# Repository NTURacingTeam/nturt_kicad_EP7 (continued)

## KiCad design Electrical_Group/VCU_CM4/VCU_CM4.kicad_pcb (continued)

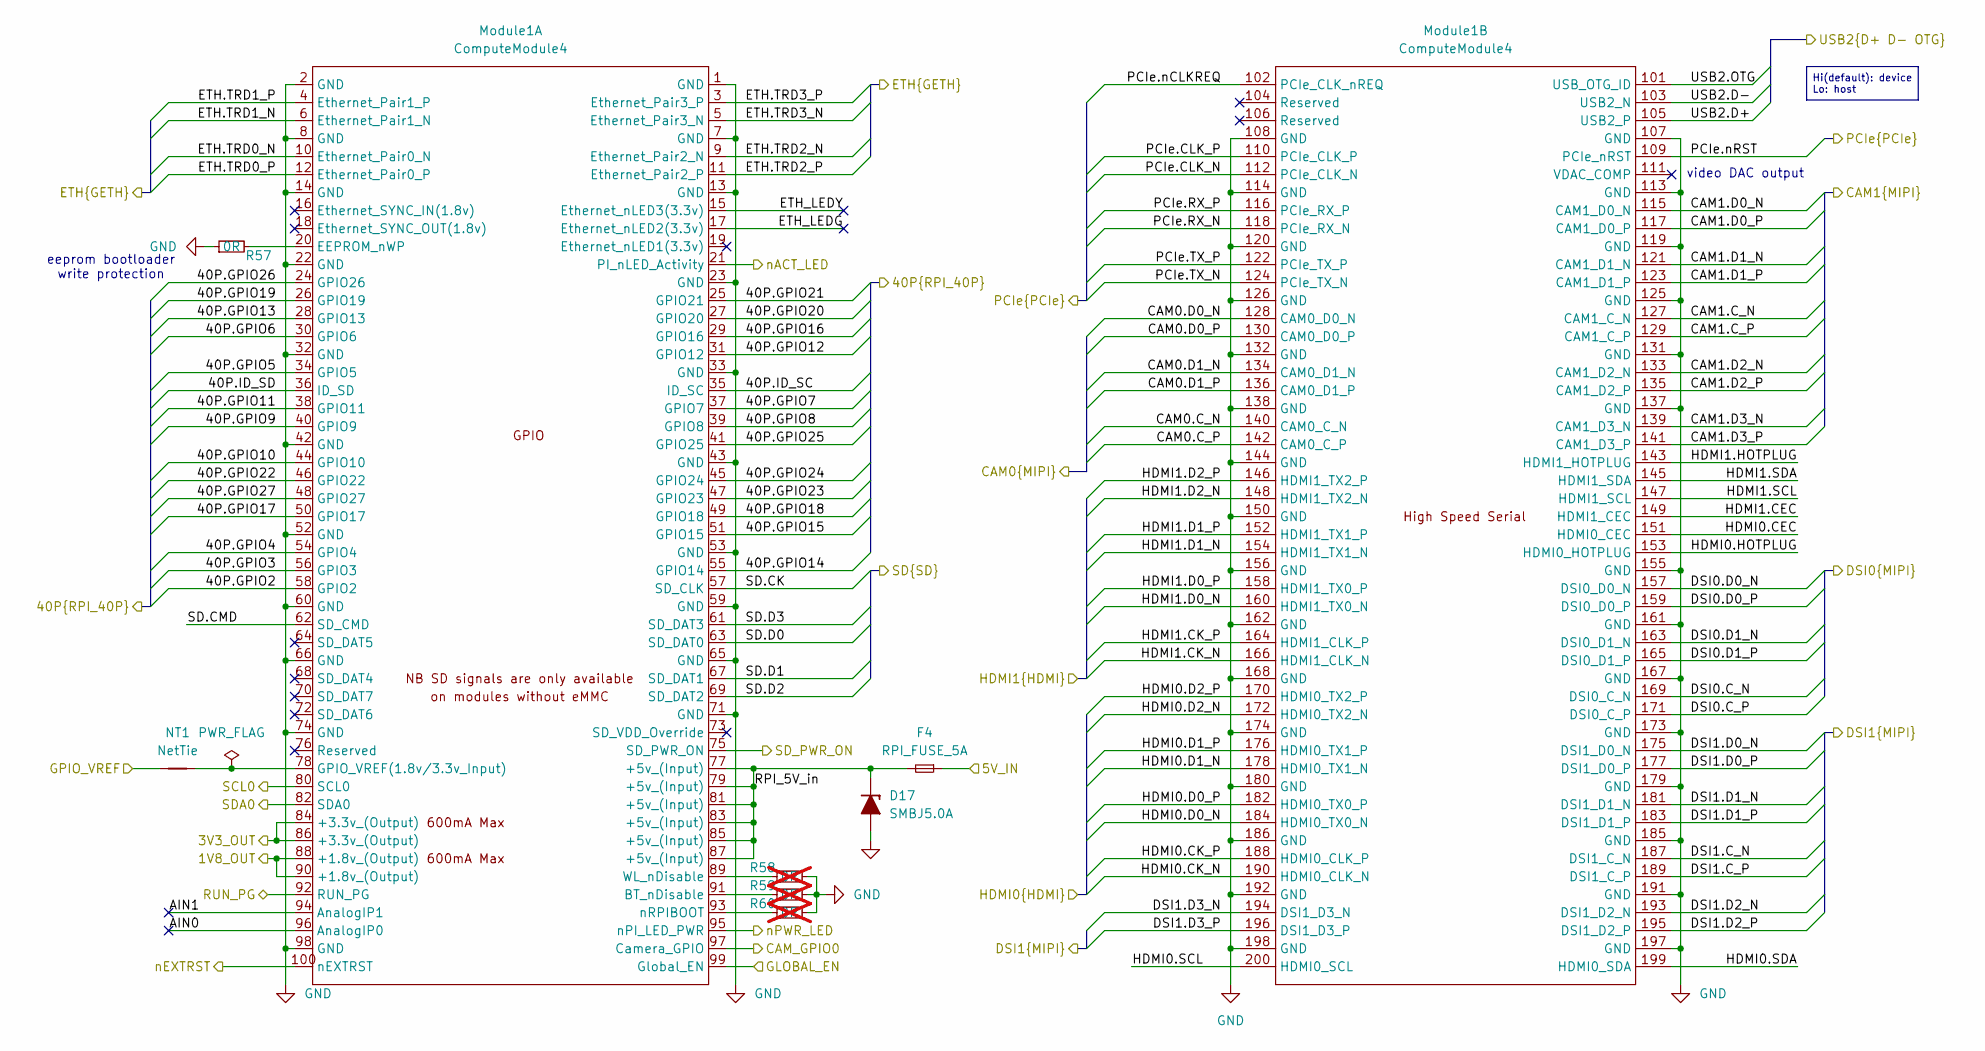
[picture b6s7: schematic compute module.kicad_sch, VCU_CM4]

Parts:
D17: SMBJ5.0A; D_SMB
F4: RPI_FUSE_5A; Fuse_1206_3216Metric_Pad1.42x1.75mm_HandSolder
Module1: ComputeModule4; Raspberry-Pi-4-Compute-Module; Part Description 100 Position Connector Receptacle, Cent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
NT1: NetTie; NetTie-2_SMD_Pad0.5mm
R57: 0R; R_0402_1005Metric
R58, R59, R60: 0R; R_0402_1005Metric; not fitted

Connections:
+1V8_CMOUT: Module1.88 (+1.8v_(Output)), Module1.90 (+1.8v_(Output))
+3V3_CMOUT: Module1.84 (+3.3v_(Output)), Module1.86 (+3.3v_(Output)), NT1.1; also elsewhere on the board
+5V_CM: F4.1; also elsewhere on the board
/computer/40P.GPIO2: Module1.58 (GPIO2)
/computer/40P.GPIO3: Module1.56 (GPIO3)
/computer/40P.GPIO4: Module1.54 (GPIO4)
/computer/40P.GPIO5: Module1.34 (GPIO5)
/computer/40P.GPIO6: Module1.30 (GPIO6)
/computer/40P.GPIO7: Module1.37 (GPIO7)
/computer/40P.GPIO8: Module1.39 (GPIO8)
/computer/40P.GPIO9: Module1.40 (GPIO9)
/computer/40P.GPIO10: Module1.44 (GPIO10)
/computer/40P.GPIO11: Module1.38 (GPIO11)
/computer/40P.GPIO12: Module1.31 (GPIO12)
/computer/40P.GPIO13: Module1.28 (GPIO13); also elsewhere on the board
/computer/40P.GPIO14: Module1.55 (GPIO14); also elsewhere on the board
/computer/40P.GPIO15: Module1.51 (GPIO15); also elsewhere on the board
/computer/40P.GPIO16: Module1.29 (GPIO16)
/computer/40P.GPIO17: Module1.50 (GPIO17); also elsewhere on the board
/computer/40P.GPIO18: Module1.49 (GPIO18); also elsewhere on the board
/computer/40P.GPIO19: Module1.26 (GPIO19); also elsewhere on the board
/computer/40P.GPIO20: Module1.27 (GPIO20); also elsewhere on the board
/computer/40P.GPIO21: Module1.25 (GPIO21); also elsewhere on the board
/computer/40P.GPIO22: Module1.46 (GPIO22); also elsewhere on the board
/computer/40P.GPIO23: Module1.47 (GPIO23)
/computer/40P.GPIO24: Module1.45 (GPIO24)
/computer/40P.GPIO25: Module1.41 (GPIO25); also elsewhere on the board
/computer/40P.GPIO26: Module1.24 (GPIO26)
/computer/40P.GPIO27: Module1.48 (GPIO27)
/computer/40P.ID_SC: Module1.35 (ID_SC); also elsewhere on the board
/computer/40P.ID_SD: Module1.36 (ID_SD); also elsewhere on the board
/computer/CAM_GPIO0: Module1.97 (Camera_GPIO); also elsewhere on the board
/computer/SCL0: Module1.80 (SCL0); also elsewhere on the board
/computer/SD.CK: Module1.57 (SD_CLK); also elsewhere on the board
/computer/SD.CMD: Module1.62 (SD_CMD); also elsewhere on the board
/computer/SD.D0: Module1.63 (SD_DAT0); also elsewhere on the board
/computer/SD.D1: Module1.67 (SD_DAT1); also elsewhere on the board
/computer/SD.D2: Module1.69 (SD_DAT2); also elsewhere on the board
/computer/SD.D3: Module1.61 (SD_DAT3); also elsewhere on the board
/computer/SDA0: Module1.82 (SDA0); also elsewhere on the board
/computer/SD_PWR_ON: Module1.75 (SD_PWR_ON); also elsewhere on the board
/computer/USB2.D+: Module1.105 (USB2_P); also elsewhere on the board
/computer/USB2.D-: Module1.103 (USB2_N); also elsewhere on the board
/computer/USB2.OTG: Module1.101 (USB_OTG_ID); also elsewhere on the board
/computer/compute module/AIN0: Module1.96 (AnalogIP0)
/computer/compute module/AIN1: Module1.94 (AnalogIP1)
/computer/compute module/CAM0.C_N: Module1.140 (CAM0_C_N)
/computer/compute module/CAM0.C_P: Module1.142 (CAM0_C_P)
/computer/compute module/CAM0.D0_N: Module1.128 (CAM0_D0_N)
/computer/compute module/CAM0.D0_P: Module1.130 (CAM0_D0_P)
/computer/compute module/CAM0.D1_N: Module1.134 (CAM0_D1_N)
/computer/compute module/CAM0.D1_P: Module1.136 (CAM0_D1_P)
/computer/compute module/CAM1.C_N: Module1.127 (CAM1_C_N); also elsewhere on the board
/computer/compute module/CAM1.C_P: Module1.129 (CAM1_C_P); also elsewhere on the board
/computer/compute module/CAM1.D0_N: Module1.115 (CAM1_D0_N); also elsewhere on the board
/computer/compute module/CAM1.D0_P: Module1.117 (CAM1_D0_P); also elsewhere on the board
/computer/compute module/CAM1.D1_N: Module1.121 (CAM1_D1_N); also elsewhere on the board
/computer/compute module/CAM1.D1_P: Module1.123 (CAM1_D1_P); also elsewhere on the board
/computer/compute module/CAM1.D2_N: Module1.133 (CAM1_D2_N); also elsewhere on the board
/computer/compute module/CAM1.D2_P: Module1.135 (CAM1_D2_P); also elsewhere on the board
/computer/compute module/CAM1.D3_N: Module1.139 (CAM1_D3_N); also elsewhere on the board
/computer/compute module/CAM1.D3_P: Module1.141 (CAM1_D3_P); also elsewhere on the board
/computer/compute module/DSI0.C_N: Module1.169 (DSI0_C_N)
/computer/compute module/DSI0.C_P: Module1.171 (DSI0_C_P)
/computer/compute module/DSI0.D0_N: Module1.157 (DSI0_D0_N)
/computer/compute module/DSI0.D0_P: Module1.159 (DSI0_D0_P)
/computer/compute module/DSI0.D1_N: Module1.163 (DSI0_D1_N)
/computer/compute module/DSI0.D1_P: Module1.165 (DSI0_D1_P)
/computer/compute module/DSI1.C_N: Module1.187 (DSI1_C_N); also elsewhere on the board
/computer/compute module/DSI1.C_P: Module1.189 (DSI1_C_P); also elsewhere on the board
/computer/compute module/DSI1.D0_N: Module1.175 (DSI1_D0_N); also elsewhere on the board
/computer/compute module/DSI1.D0_P: Module1.177 (DSI1_D0_P); also elsewhere on the board
/computer/compute module/DSI1.D1_N: Module1.181 (DSI1_D1_N); also elsewhere on the board
/computer/compute module/DSI1.D1_P: Module1.183 (DSI1_D1_P); also elsewhere on the board
/computer/compute module/DSI1.D2_N: Module1.193 (DSI1_D2_N); also elsewhere on the board
/computer/compute module/DSI1.D2_P: Module1.195 (DSI1_D2_P); also elsewhere on the board
/computer/compute module/DSI1.D3_N: Module1.194 (DSI1_D3_N); also elsewhere on the board
/computer/compute module/DSI1.D3_P: Module1.196 (DSI1_D3_P); also elsewhere on the board
/computer/compute module/ETH.TRD0_N: Module1.10 (Ethernet_Pair0_N)
/computer/compute module/ETH.TRD0_P: Module1.12 (Ethernet_Pair0_P)
/computer/compute module/ETH.TRD1_N: Module1.6 (Ethernet_Pair1_N)
/computer/compute module/ETH.TRD1_P: Module1.4 (Ethernet_Pair1_P)
/computer/compute module/ETH.TRD2_N: Module1.9 (Ethernet_Pair2_N)
/computer/compute module/ETH.TRD2_P: Module1.11 (Ethernet_Pair2_P)
/computer/compute module/ETH.TRD3_N: Module1.5 (Ethernet_Pair3_N)
/computer/compute module/ETH.TRD3_P: Module1.3 (Ethernet_Pair3_P)
/computer/compute module/ETH_LEDG: Module1.17 (Ethernet_nLED2(3.3v))
/computer/compute module/ETH_LEDY: Module1.15 (Ethernet_nLED3(3.3v))
/computer/compute module/GLOBAL_EN: Module1.99 (Global_EN); also elsewhere on the board
/computer/compute module/HDMI0.CEC: Module1.151 (HDMI0_CEC)
/computer/compute module/HDMI0.CK_N: Module1.190 (HDMI0_CLK_N)
/computer/compute module/HDMI0.CK_P: Module1.188 (HDMI0_CLK_P)
/computer/compute module/HDMI0.D0_N: Module1.184 (HDMI0_TX0_N)
/computer/compute module/HDMI0.D0_P: Module1.182 (HDMI0_TX0_P)
/computer/compute module/HDMI0.D1_N: Module1.178 (HDMI0_TX1_N)
/computer/compute module/HDMI0.D1_P: Module1.176 (HDMI0_TX1_P)
/computer/compute module/HDMI0.D2_N: Module1.172 (HDMI0_TX2_N)
/computer/compute module/HDMI0.D2_P: Module1.170 (HDMI0_TX2_P)
/computer/compute module/HDMI0.HOTPLUG: Module1.153 (HDMI0_HOTPLUG)
/computer/compute module/HDMI0.SCL: Module1.200 (HDMI0_SCL)
/computer/compute module/HDMI0.SDA: Module1.199 (HDMI0_SDA)
/computer/compute module/HDMI1.CEC: Module1.149 (HDMI1_CEC)
/computer/compute module/HDMI1.CK_N: Module1.166 (HDMI1_CLK_N)
/computer/compute module/HDMI1.CK_P: Module1.164 (HDMI1_CLK_P)
/computer/compute module/HDMI1.D0_N: Module1.160 (HDMI1_TX0_N)
/computer/compute module/HDMI1.D0_P: Module1.158 (HDMI1_TX0_P)
/computer/compute module/HDMI1.D1_N: Module1.154 (HDMI1_TX1_N)
/computer/compute module/HDMI1.D1_P: Module1.152 (HDMI1_TX1_P)
/computer/compute module/HDMI1.D2_N: Module1.148 (HDMI1_TX2_N)
/computer/compute module/HDMI1.D2_P: Module1.146 (HDMI1_TX2_P)
/computer/compute module/HDMI1.HOTPLUG: Module1.143 (HDMI1_HOTPLUG)
/computer/compute module/HDMI1.SCL: Module1.147 (HDMI1_SCL)
/computer/compute module/HDMI1.SDA: Module1.145 (HDMI1_SDA)
/computer/compute module/PCIe.CLK_N: Module1.112 (PCIe_CLK_N)
/computer/compute module/PCIe.CLK_P: Module1.110 (PCIe_CLK_P)
/computer/compute module/PCIe.RX_N: Module1.118 (PCIe_RX_N)
/computer/compute module/PCIe.RX_P: Module1.116 (PCIe_RX_P)
/computer/compute module/PCIe.TX_N: Module1.124 (PCIe_TX_N)
/computer/compute module/PCIe.TX_P: Module1.122 (PCIe_TX_P)
/computer/compute module/PCIe.nCLKREQ: Module1.102 (PCIe_CLK_nREQ)
/computer/compute module/PCIe.nRST: Module1.109 (PCIe_nRST)
/computer/compute module/RPI_5V_in: D17.1 (K), F4.2, Module1.77 (+5v_(Input)), Module1.79 (+5v_(Input)), Module1.81 (+5v_(Input)), Module1.83 (+5v_(Input)), Module1.85 (+5v_(Input)), Module1.87 (+5v_(Input))
/computer/compute module/RUN_PG: Module1.92 (RUN_PG); also elsewhere on the board
/computer/compute module/nACT_LED: Module1.21 (PI_nLED_Activity); also elsewhere on the board
/computer/compute module/nEXTRST: Module1.100 (nEXTRST)
/computer/compute module/nPWR_LED: Module1.95 (nPI_LED_PWR); also elsewhere on the board
GND: D17.2 (A), Module1.1 (GND), Module1.2 (GND), Module1.7 (GND), Module1.8 (GND), Module1.13 (GND), Module1.14 (GND), Module1.22 (GND), Module1.23 (GND), Module1.32 (GND), Module1.33 (GND), Module1.42 (GND), Module1.43 (GND), Module1.52 (GND), Module1.53 (GND), Module1.59 (GND), Module1.60 (GND), Module1.65 (GND), Module1.66 (GND), Module1.71 (GND), Module1.74 (GND), Module1.98 (GND), Module1.107 (GND), Module1.108 (GND), Module1.113 (GND), Module1.114 (GND), Module1.119 (GND), Module1.120 (GND), Module1.125 (GND), Module1.126 (GND), Module1.131 (GND), Module1.132 (GND), Module1.137 (GND), Module1.138 (GND), Module1.144 (GND), Module1.150 (GND), Module1.155 (GND), Module1.156 (GND), Module1.161 (GND), Module1.162 (GND), Module1.167 (GND), Module1.168 (GND), Module1.173 (GND), Module1.174 (GND), Module1.179 (GND), Module1.180 (GND), Module1.185 (GND), Module1.186 (GND), Module1.191 (GND), Module1.192 (GND), Module1.197 (GND), Module1.198 (GND), R57.1, R58.2, R59.2, R60.2; also elsewhere on the board
unnamed: Module1.91 (BT_nDisable), R59.1
unnamed: Module1.20 (EEPROM_nWP), R57.2
unnamed: Module1.78 (GPIO_VREF(1.8v/3.3v_Input)), NT1.2
unnamed: Module1.89 (WL_nDisable), R58.1
unnamed: Module1.93 (nRPIBOOT), R60.1

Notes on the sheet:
eeprom bootloader write protection
video DAC output
Hi(default): device Lo: host

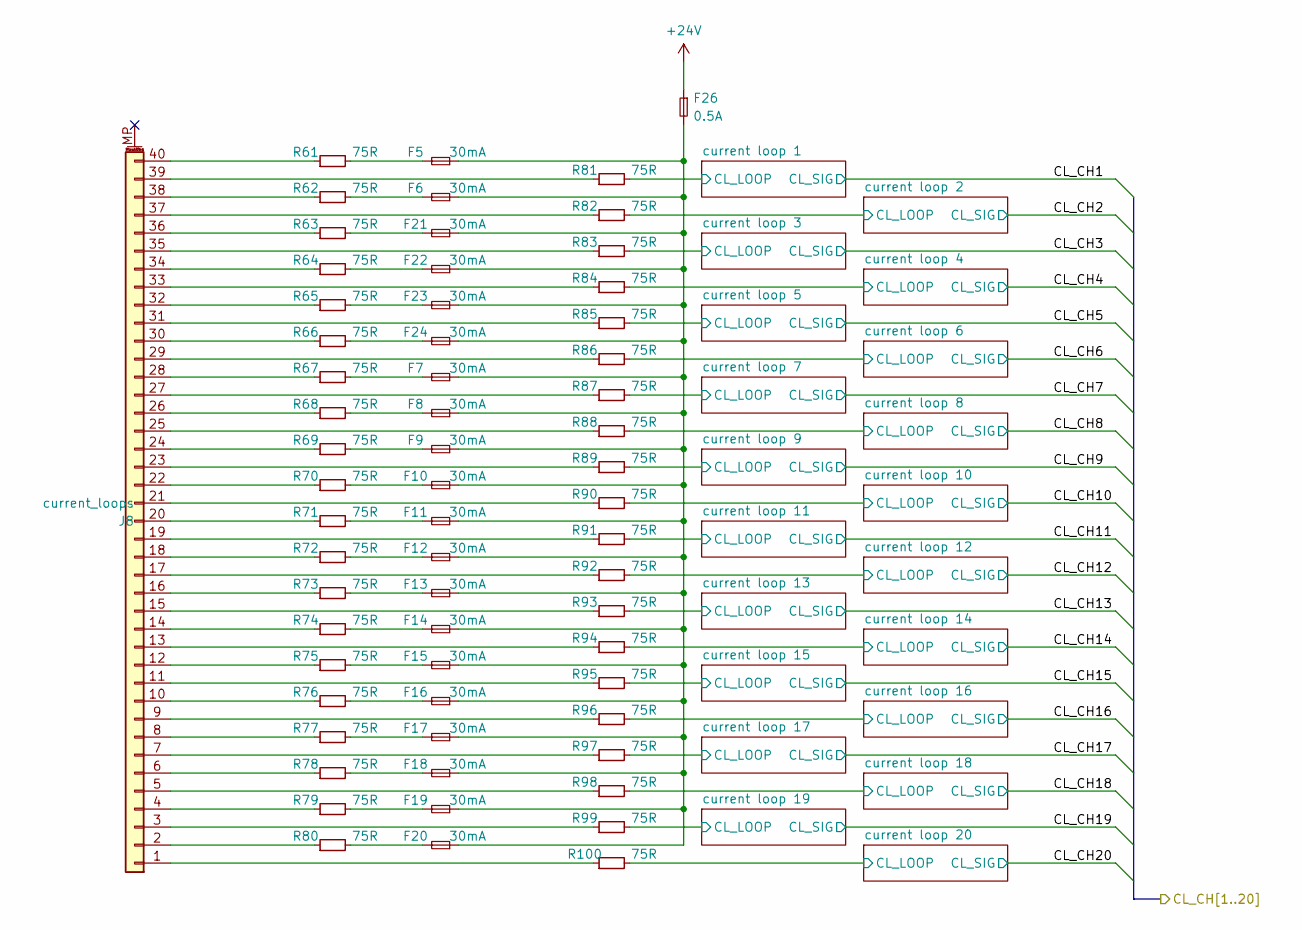
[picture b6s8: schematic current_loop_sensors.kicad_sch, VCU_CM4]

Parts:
F5, F6, F7, F8, F9, F10, F11, F12, F13, F14, F15, F16, F17, F18, F19, F20, F21, F22, F23, F24: 30mA; Fuse_0805_2012Metric_Pad1.15x1.40mm_HandSolder
F26: 0.5A; Fuse_1206_3216Metric
J8: current_loops; Amphenol_F32Q-1A7x1-11040_1x40-1MP_P0.5mm_Horizontal
R61, R62, R63, R64, R65, R66, R67, R68, R69, R70, R71, R72, R73, R74, R75, R76, R77, R78, R79, R80: 75R; R_0603_1608Metric_Pad0.98x0.95mm_HandSolder
R81, R82, R83, R84, R85, R86, R87, R88, R89, R90, R91, R92, R93, R94, R95, R96, R97, R98, R99, R100: 75R; R_0603_1608Metric

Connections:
+24V: F26.1; also elsewhere on the board
/vcu mcu/current loop sensors/current loop 1/CL_LOOP: R81.2; also elsewhere on the board
/vcu mcu/current loop sensors/current loop 2/CL_LOOP: R82.2; also elsewhere on the board
/vcu mcu/current loop sensors/current loop 3/CL_LOOP: R83.2; also elsewhere on the board
/vcu mcu/current loop sensors/current loop 4/CL_LOOP: R84.2; also elsewhere on the board
/vcu mcu/current loop sensors/current loop 5/CL_LOOP: R85.2; also elsewhere on the board
/vcu mcu/current loop sensors/current loop 6/CL_LOOP: R86.2; also elsewhere on the board
/vcu mcu/current loop sensors/current loop 7/CL_LOOP: R87.2; also elsewhere on the board
/vcu mcu/current loop sensors/current loop 8/CL_LOOP: R88.2; also elsewhere on the board
/vcu mcu/current loop sensors/current loop 9/CL_LOOP: R89.2; also elsewhere on the board
/vcu mcu/current loop sensors/current loop 10/CL_LOOP: R90.2; also elsewhere on the board
/vcu mcu/current loop sensors/current loop 11/CL_LOOP: R91.2; also elsewhere on the board
/vcu mcu/current loop sensors/current loop 12/CL_LOOP: R92.2; also elsewhere on the board
/vcu mcu/current loop sensors/current loop 13/CL_LOOP: R93.2; also elsewhere on the board
/vcu mcu/current loop sensors/current loop 14/CL_LOOP: R94.2; also elsewhere on the board
/vcu mcu/current loop sensors/current loop 15/CL_LOOP: R95.2; also elsewhere on the board
/vcu mcu/current loop sensors/current loop 16/CL_LOOP: R96.2; also elsewhere on the board
/vcu mcu/current loop sensors/current loop 17/CL_LOOP: R97.2; also elsewhere on the board
/vcu mcu/current loop sensors/current loop 18/CL_LOOP: R98.2; also elsewhere on the board
/vcu mcu/current loop sensors/current loop 19/CL_LOOP: R99.2; also elsewhere on the board
/vcu mcu/current loop sensors/current loop 20/CL_LOOP: R100.2; also elsewhere on the board
unnamed: F5.2, R61.2
unnamed: F6.2, R62.2
unnamed: F7.2, R67.2
unnamed: F8.2, R68.2
unnamed: F9.2, R69.2
unnamed: F5.1, F6.1, F7.1, F8.1, F9.1, F10.1, F11.1, F12.1, F13.1, F14.1, F15.1, F16.1, F17.1, F18.1, F19.1, F20.1, F21.1, F22.1, F23.1, F24.1, F26.2
unnamed: F10.2, R70.2
unnamed: F11.2, R71.2
unnamed: F12.2, R72.2
unnamed: F13.2, R73.2
unnamed: F14.2, R74.2
unnamed: F15.2, R75.2
unnamed: F16.2, R76.2
unnamed: F17.2, R77.2
unnamed: F18.2, R78.2
unnamed: F19.2, R79.2
unnamed: F20.2, R80.2
unnamed: F21.2, R63.2
unnamed: F22.2, R64.2
unnamed: F23.2, R65.2
unnamed: F24.2, R66.2
unnamed: J8.1, R100.1
unnamed: J8.2, R80.1
unnamed: J8.3, R99.1
unnamed: J8.4, R79.1
unnamed: J8.5, R98.1
unnamed: J8.6, R78.1
unnamed: J8.7, R97.1
unnamed: J8.8, R77.1
unnamed: J8.9, R96.1
unnamed: J8.10, R76.1
unnamed: J8.11, R95.1
unnamed: J8.12, R75.1
unnamed: J8.13, R94.1
unnamed: J8.14, R74.1
unnamed: J8.15, R93.1
unnamed: J8.16, R73.1
unnamed: J8.17, R92.1
unnamed: J8.18, R72.1
unnamed: J8.19, R91.1
unnamed: J8.20, R71.1
unnamed: J8.21, R90.1
unnamed: J8.22, R70.1
unnamed: J8.23, R89.1
unnamed: J8.24, R69.1
unnamed: J8.25, R88.1
unnamed: J8.26, R68.1
unnamed: J8.27, R87.1
unnamed: J8.28, R67.1
unnamed: J8.29, R86.1
unnamed: J8.30, R66.1
unnamed: J8.31, R85.1
unnamed: J8.32, R65.1
unnamed: J8.33, R84.1
unnamed: J8.34, R64.1
unnamed: J8.35, R83.1
unnamed: J8.36, R63.1
unnamed: J8.37, R82.1
unnamed: J8.38, R62.1
unnamed: J8.39, R81.1
unnamed: J8.40, R61.1

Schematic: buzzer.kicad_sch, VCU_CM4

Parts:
D32: WHITE LED; LED_0603_1608Metric
Q3: 2N7002; SOT-23
R142: 100; R_0402_1005Metric
R143: 100k; R_0402_1005Metric
R144: 10k; R_0402_1005Metric
TP13: BUZZER_P; edge_pad_1.4mm_0.7mm
TP14: BUZZER_N; edge_pad_1.4mm_0.7mm

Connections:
+24V: D32.2 (A), TP13.1; also elsewhere on the board
/vcu mcu/buzzer/buzzer_outbox: Q3.3 (D), R144.1, TP14.1
/vcu mcu/buzzer_gate: R142.2; also elsewhere on the board
GND: Q3.2 (S), R143.1; also elsewhere on the board
unnamed: D32.1 (K), R144.2
unnamed: Q3.1 (G), R142.1, R143.2

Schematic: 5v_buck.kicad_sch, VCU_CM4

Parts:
C9: 10u 50V; C_1206_3216Metric
C10: 0u1; C_0603_1608Metric
C11: 10n; C_0603_1608Metric
C12, C13, C14, C15, C16, C17: 47u 10V; C_1206_3216Metric
D4: SS54; D_SMA
D5: SMBJ5.0A; D_SMB
F3: 3A; Fuse_1206_3216Metric_Pad1.42x1.75mm_HandSolder
L2: 22uH 3.7A (SMDRI129-220MT); L_Bourns_SRR1260
R13: 47k; R_0402_1005Metric
R14: 15k; R_0402_1005Metric
R165: 10k; R_0402_1005Metric
R167: 1k; R_0402_1005Metric
U3: TPS5430DDA; TI_SO-PowerPAD-8

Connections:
+5V_CM: D5.1 (K), F3.2; also elsewhere on the board
+24V: C9.1, C10.2, R165.1, U3.7 (VIN); also elsewhere on the board
GND: C9.2, C10.1, C12.2, C13.2, C14.2, C15.2, C16.2, C17.2, D4.2 (A), D5.2 (A), R14.2, R167.2, U3.6 (GND), U3.9 (GNDPAD); also elsewhere on the board
unnamed: C12.1, C13.1, C14.1, C15.1, C16.1, C17.1, F3.1, L2.2, R13.1
unnamed: C11.2, D4.1 (K), L2.1, U3.8 (PH)
unnamed: C11.1, U3.1 (BOOT)
unnamed: R165.2, R167.1, U3.5 (EN)
unnamed: R13.2, R14.1, U3.4 (VSENSE)

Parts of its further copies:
C111: 10u 50V; C_1206_3216Metric
C112: 0u1; C_0603_1608Metric
C113: 10n; C_0603_1608Metric
C114, C115, C116, C117, C118, C119: 47u 10V; C_1206_3216Metric
D33: SS54; D_SMA
D34: SMBJ5.0A; D_SMB
F25: 3A; Fuse_1206_3216Metric_Pad1.42x1.75mm_HandSolder
L3: 22uH 3.7A (SMDRI129-220MT); L_Bourns_SRR1260
R145: 47k; R_0402_1005Metric
R146: 15k; R_0402_1005Metric
R166: 10k; R_0402_1005Metric
R168: 1k; R_0402_1005Metric
U13: TPS5430DDA; TI_SO-PowerPAD-8

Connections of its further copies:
+5V: D34.1 (K), F25.2; also elsewhere on the board
+24V: C111.1, C112.2, R166.1, U13.7 (VIN); also elsewhere on the board
GND: C111.2, C112.1, C114.2, C115.2, C116.2, C117.2, C118.2, C119.2, D33.2 (A), D34.2 (A), R146.2, R168.2, U13.6 (GND), U13.9 (GNDPAD); also elsewhere on the board
unnamed: C114.1, C115.1, C116.1, C117.1, C118.1, C119.1, F25.1, L3.2, R145.1
unnamed: C113.2, D33.1 (K), L3.1, U13.8 (PH)
unnamed: C113.1, U13.1 (BOOT)
unnamed: R166.2, R168.1, U13.5 (EN)
unnamed: R145.2, R146.1, U13.4 (VSENSE)

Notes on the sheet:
FB Vref=1.221 R_FBB = 10k ~ 100k possible R_FBT, R_FBB 16,5.1 => 5.05 V 18, 5.6 => 5.146 V 7.5, 2.4 => 5.037 V 5.1, 1.6 => 5.113 V

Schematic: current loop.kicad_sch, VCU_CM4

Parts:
C30: 1u; C_0402_1005Metric
C31: 10u; C_0402_1005Metric
D12: zener 3.6V; D_SOD-323
R28: 150R 1%; R_0603_1608Metric
R29: 100R; R_0603_1608Metric

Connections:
/vcu mcu/CL_CH1: C31.1, D12.1 (K), R29.2; also elsewhere on the board
/vcu mcu/current loop sensors/current loop 1/CL_LOOP: C30.1, R28.1, R29.1; also elsewhere on the board
GND: C30.2, C31.2, D12.2 (A), R28.2; also elsewhere on the board

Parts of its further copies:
C20, C22, C24, C26, C28, C56, C58, C60, C62, C64, C66, C68, C70, C72, C74, C76, C78, C80, C109: 1u; C_0402_1005Metric
C21, C23, C25, C27, C29, C57, C59, C61, C63, C65, C67, C69, C71, C73, C75, C77, C79, C81, C110: 10u; C_0402_1005Metric
D7, D8, D9, D10, D11, D18, D19, D20, D21, D22, D23, D24, D25, D26, D27, D28, D29, D30, D31: zener 3.6V; D_SOD-323
R18, R20, R22, R24, R26, R101, R103, R105, R107, R109, R111, R113, R115, R117, R119, R121, R123, R125, R140: 150R 1%; R_0603_1608Metric
R19, R21, R23, R25, R27, R102, R104, R106, R108, R110, R112, R114, R116, R118, R120, R122, R124, R126, R141: 100R; R_0603_1608Metric

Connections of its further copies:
/vcu mcu/CL_CH2: C57.1, D18.1 (K), R102.2; also elsewhere on the board
/vcu mcu/CL_CH3: C59.1, D19.1 (K), R104.2; also elsewhere on the board
/vcu mcu/CL_CH4: C61.1, D20.1 (K), R106.2; also elsewhere on the board
/vcu mcu/CL_CH5: C63.1, D21.1 (K), R108.2; also elsewhere on the board
/vcu mcu/CL_CH6: C65.1, D22.1 (K), R110.2; also elsewhere on the board
/vcu mcu/CL_CH7: C67.1, D23.1 (K), R112.2; also elsewhere on the board
/vcu mcu/CL_CH8: C69.1, D24.1 (K), R114.2; also elsewhere on the board
/vcu mcu/CL_CH9: C71.1, D25.1 (K), R116.2; also elsewhere on the board
/vcu mcu/CL_CH10: C73.1, D26.1 (K), R118.2; also elsewhere on the board
/vcu mcu/CL_CH11: C75.1, D27.1 (K), R120.2; also elsewhere on the board
/vcu mcu/CL_CH12: C77.1, D28.1 (K), R122.2; also elsewhere on the board
/vcu mcu/CL_CH13: C79.1, D29.1 (K), R124.2; also elsewhere on the board
/vcu mcu/CL_CH14: C81.1, D30.1 (K), R126.2; also elsewhere on the board
/vcu mcu/CL_CH15: C110.1, D31.1 (K), R141.2; also elsewhere on the board
/vcu mcu/CL_CH16: C21.1, D7.1 (K), R19.2; also elsewhere on the board
/vcu mcu/CL_CH17: C23.1, D8.1 (K), R21.2; also elsewhere on the board
/vcu mcu/CL_CH18: C25.1, D9.1 (K), R23.2; also elsewhere on the board
/vcu mcu/CL_CH19: C27.1, D10.1 (K), R25.2; also elsewhere on the board
/vcu mcu/CL_CH20: C29.1, D11.1 (K), R27.2; also elsewhere on the board
/vcu mcu/current loop sensors/current loop 2/CL_LOOP: C56.1, R101.1, R102.1; also elsewhere on the board
/vcu mcu/current loop sensors/current loop 3/CL_LOOP: C58.1, R103.1, R104.1; also elsewhere on the board
/vcu mcu/current loop sensors/current loop 4/CL_LOOP: C60.1, R105.1, R106.1; also elsewhere on the board
/vcu mcu/current loop sensors/current loop 5/CL_LOOP: C62.1, R107.1, R108.1; also elsewhere on the board
/vcu mcu/current loop sensors/current loop 6/CL_LOOP: C64.1, R109.1, R110.1; also elsewhere on the board
/vcu mcu/current loop sensors/current loop 7/CL_LOOP: C66.1, R111.1, R112.1; also elsewhere on the board
/vcu mcu/current loop sensors/current loop 8/CL_LOOP: C68.1, R113.1, R114.1; also elsewhere on the board
/vcu mcu/current loop sensors/current loop 9/CL_LOOP: C70.1, R115.1, R116.1; also elsewhere on the board
/vcu mcu/current loop sensors/current loop 10/CL_LOOP: C72.1, R117.1, R118.1; also elsewhere on the board
/vcu mcu/current loop sensors/current loop 11/CL_LOOP: C74.1, R119.1, R120.1; also elsewhere on the board
/vcu mcu/current loop sensors/current loop 12/CL_LOOP: C76.1, R121.1, R122.1; also elsewhere on the board
/vcu mcu/current loop sensors/current loop 13/CL_LOOP: C78.1, R123.1, R124.1; also elsewhere on the board
/vcu mcu/current loop sensors/current loop 14/CL_LOOP: C80.1, R125.1, R126.1; also elsewhere on the board
/vcu mcu/current loop sensors/current loop 15/CL_LOOP: C109.1, R140.1, R141.1; also elsewhere on the board
/vcu mcu/current loop sensors/current loop 16/CL_LOOP: C20.1, R18.1, R19.1; also elsewhere on the board
/vcu mcu/current loop sensors/current loop 17/CL_LOOP: C22.1, R20.1, R21.1; also elsewhere on the board
/vcu mcu/current loop sensors/current loop 18/CL_LOOP: C24.1, R22.1, R23.1; also elsewhere on the board
/vcu mcu/current loop sensors/current loop 19/CL_LOOP: C26.1, R24.1, R25.1; also elsewhere on the board
/vcu mcu/current loop sensors/current loop 20/CL_LOOP: C28.1, R26.1, R27.1; also elsewhere on the board
GND: C20.2, C21.2, C22.2, C23.2, C24.2, C25.2, C26.2, C27.2, C28.2, C29.2, C56.2, C57.2, C58.2, C59.2, C60.2, C61.2, C62.2, C63.2, C64.2, C65.2, C66.2, C67.2, C68.2, C69.2, C70.2, C71.2, C72.2, C73.2, C74.2, C75.2, C76.2, C77.2, C78.2, C79.2, C80.2, C81.2, C109.2, C110.2, D7.2 (A), D8.2 (A), D9.2 (A), D10.2 (A), D11.2 (A), D18.2 (A), D19.2 (A), D20.2 (A), D21.2 (A), D22.2 (A), D23.2 (A), D24.2 (A), D25.2 (A), D26.2 (A), D27.2 (A), D28.2 (A), D29.2 (A), D30.2 (A), D31.2 (A), R18.2, R20.2, R22.2, R24.2, R26.2, R101.2, R103.2, R105.2, R107.2, R109.2, R111.2, R113.2, R115.2, R117.2, R119.2, R121.2, R123.2, R125.2, R140.2; also elsewhere on the board

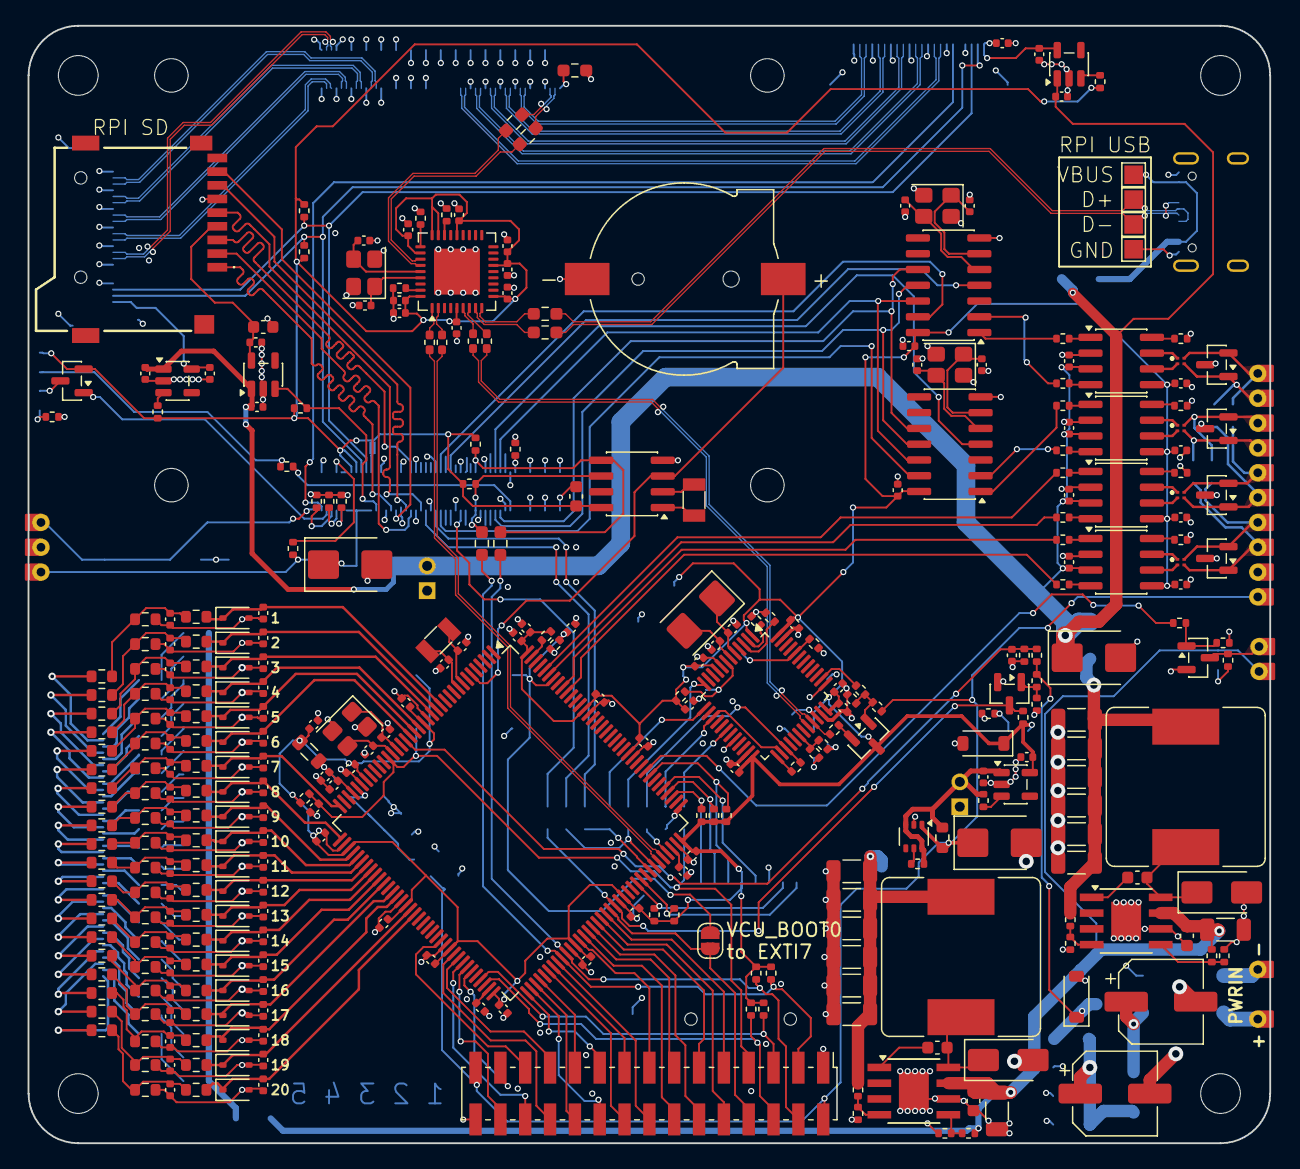
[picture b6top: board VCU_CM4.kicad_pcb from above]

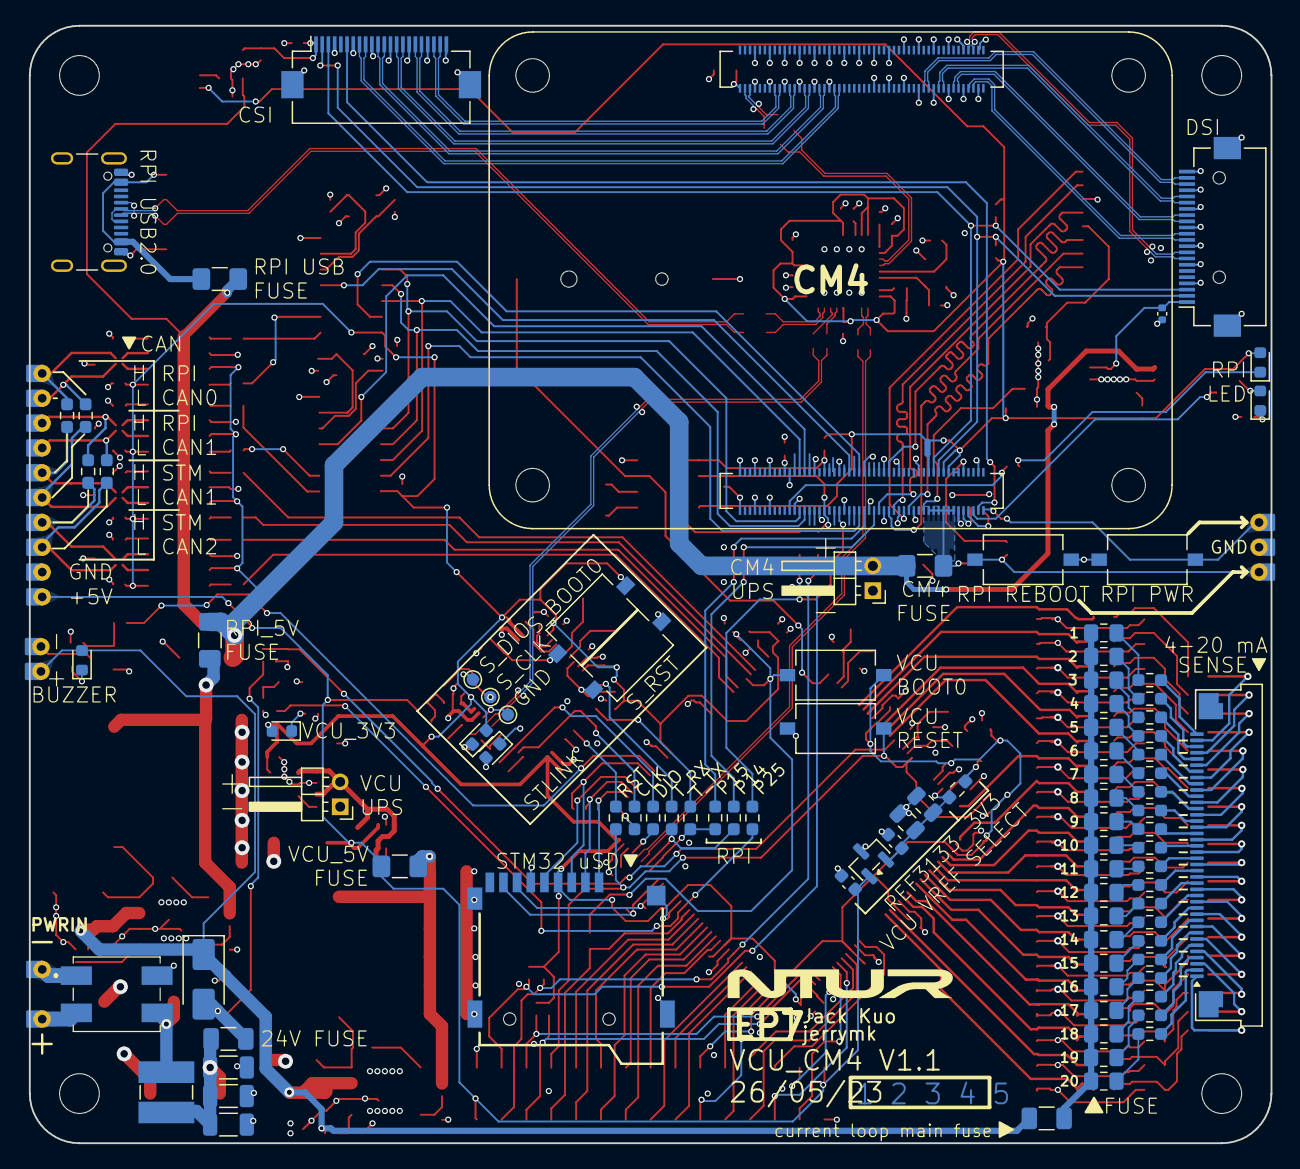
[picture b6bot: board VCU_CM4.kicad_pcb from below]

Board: 4 copper layers, 100.0 x 90.0 mm, 461 parts (95 on the bottom side), 327 nets.

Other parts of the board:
C18, C19, C120, C121, C136, C137, C143, C144: 0u1; C_0402_1005Metric
D6, D35, D36, D38: NUP2105L; SOT-23
FL2, FL3, FL4, FL5: EXC14CE121U; EXCX4CE900U
R15, R16, R147, R148, R155, R156, R160, R161: 22R; R_0402_1005Metric
R17, R149, R158, R162: 10k; R_0402_1005Metric
U4, U14, U17, U19: TCAN1042VDRQ1; SOIC-8_3.9x4.9mm_P1.27mm

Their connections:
+3V3: C19.1, C121.1, C137.1, C144.1, U4.5 (VIO), U14.5 (VIO), U17.5 (VIO), U19.5 (VIO); also elsewhere on the board
+5V_CM: C18.1, C120.1, C136.1, C143.1, U4.3 (VCC), U14.3 (VCC), U17.3 (VCC), U19.3 (VCC); also elsewhere on the board
/RPI CAN0/CAN.RX: R156.1; also elsewhere on the board
/RPI CAN0/CAN.TX: R155.1; also elsewhere on the board
/RPI CAN0/CAN_H: D36.2 (K), FL4.4; also elsewhere on the board
/RPI CAN0/CAN_L: D36.1 (K), FL4.3; also elsewhere on the board
/RPI CAN1/CAN.RX: R148.1; also elsewhere on the board
/RPI CAN1/CAN.TX: R147.1; also elsewhere on the board
/RPI CAN1/CAN_H: D35.2 (K), FL3.4; also elsewhere on the board
/RPI CAN1/CAN_L: D35.1 (K), FL3.3; also elsewhere on the board
/STM32 CAN1/CAN.RX: R161.1; also elsewhere on the board
/STM32 CAN1/CAN.TX: R160.1; also elsewhere on the board
/STM32 CAN1/CAN_H: D38.2 (K), FL5.4; also elsewhere on the board
/STM32 CAN1/CAN_L: D38.1 (K), FL5.3; also elsewhere on the board
/STM32 CAN2/CAN.RX: R16.1; also elsewhere on the board
/STM32 CAN2/CAN.TX: R15.1; also elsewhere on the board
/STM32 CAN2/CAN_H: D6.2 (K), FL2.4; also elsewhere on the board
/STM32 CAN2/CAN_L: D6.1 (K), FL2.3; also elsewhere on the board
GND: C18.2, C19.2, C120.2, C121.2, C136.2, C137.2, C143.2, C144.2, D6.3 (A), D35.3 (A), D36.3 (A), D38.3 (A), R17.2, R149.2, R158.2, R162.2, U4.2 (GND), U14.2 (GND), U17.2 (GND), U19.2 (GND); also elsewhere on the board
unnamed: FL2.1, U4.7 (CANH)
unnamed: FL2.2, U4.6 (CANL)
unnamed: R16.2, U4.4 (RXD)
unnamed: R17.1, U4.8 (STB)
unnamed: R15.2, U4.1 (TXD)
unnamed: FL3.1, U14.7 (CANH)
unnamed: FL3.2, U14.6 (CANL)
unnamed: R148.2, U14.4 (RXD)
unnamed: R149.1, U14.8 (STB)
unnamed: R147.2, U14.1 (TXD)
unnamed: FL4.1, U17.7 (CANH)
unnamed: FL4.2, U17.6 (CANL)
unnamed: R156.2, U17.4 (RXD)
unnamed: R158.1, U17.8 (STB)
unnamed: R155.2, U17.1 (TXD)
unnamed: FL5.1, U19.7 (CANH)
unnamed: FL5.2, U19.6 (CANL)
unnamed: R161.2, U19.4 (RXD)
unnamed: R162.1, U19.8 (STB)
unnamed: R160.2, U19.1 (TXD)

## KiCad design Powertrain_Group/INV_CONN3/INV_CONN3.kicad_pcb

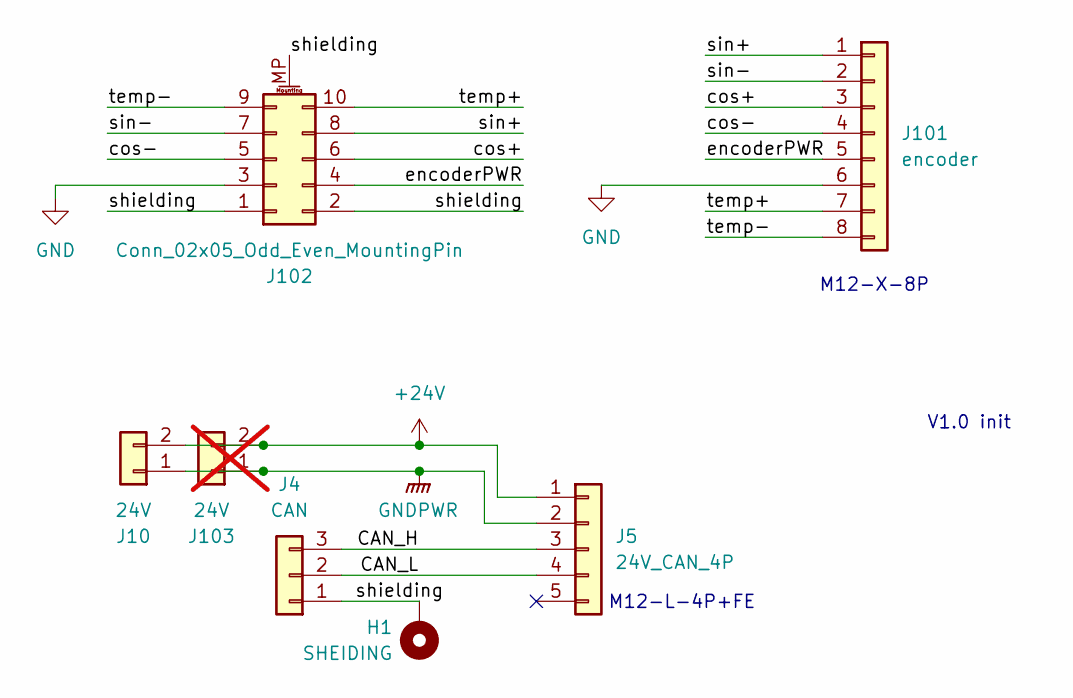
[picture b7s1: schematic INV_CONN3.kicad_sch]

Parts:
H1: SHEIDING; MountingHole_3.2mm_M3_Pad_Via
J4: CAN; JST_XA_S03B-XASK-1_1x03_P2.50mm_Horizontal
J5: 24V_CAN_4P; NianYeong-M12-L-F5P
J10: 24V; JST_VH_B2P-VH_1x02_P3.96mm_Vertical
J101: encoder; NianYeong-M12-X-F4P
J102: Conn_02x05_Odd_Even_MountingPin; CONN_2202050000-SD_10P_MOL
J103: 24V; JST_VH_B2P-VH_1x02_P3.96mm_Vertical; not fitted

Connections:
+24V: J5.1, J10.2, J103.2
/CAN_H: J4.3, J5.3
/CAN_L: J4.2, J5.4
/cos+: J101.3, J102.6
/cos-: J101.4, J102.5
/encoderPWR: J101.5, J102.4
/shielding: H1.1, J4.1, J102.1, J102.2, J102.MP (MountPin)
/sin+: J101.1, J102.8
/sin-: J101.2, J102.7
/temp+: J101.7, J102.10
/temp-: J101.8, J102.9
GND: J101.6, J102.3
GNDPWR: J5.2, J10.1, J103.1

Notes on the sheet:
V1.0 init
M12-L-4P+FE
M12-X-8P
